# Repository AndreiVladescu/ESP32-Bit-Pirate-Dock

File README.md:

<div align="center">

# ESP32-Bit-Pirate-Hardware

</div>

**ESP32-Bit-Pirate-Dock** is an open-source carrier board for the Espressif ESP32-S3 DevKit, designed to complement the [ESP32-Bit-Pirate](https://github.com/geo-tp/ESP32-Bit-Pirate) firmware by [geo-tp](https://github.com/geo-tp).

It provides level and voltage translation between the 3.3V ESP32-S3 and external peripherals, with support for **1.8V**, **3.3V**, and **5V** operation. See the [Hardware status](#-hardware-status) section for the current revision, and grab the [fabrication files](#-manufacturing-and-assembly) to build your own.

<div align="center">

</div>

## 🙏 Thanks to PCBWay

A big thank you to [**PCBWay**](https://www.pcbway.com/) for sponsoring and manufacturing the PCBs for this project. Their high-quality fabrication and assembly made bringing this dock to life possible. You can buy the Dock [here](https://www.pcbway.com/project/shareproject/ESP32_Bit_Pirate_Dock_ca02ded7.html) and support the project.

<div align="center">

</div>

## ✨ Features

- **Level & voltage translation** between the 3.3V ESP32-S3 and external peripherals.
- **Selectable I/O voltage:** 1.8V, 3.3V, and 5V operation.
- **Carrier board** for the original ESP32-S3-DevKitC-1 as well as third-party clones.
- **Designed as a companion** to the [ESP32-Bit-Pirate](https://github.com/geo-tp/ESP32-Bit-Pirate) multi-protocol firmware.
- **Fully open-source hardware** — schematic, PCB layout, gerbers, and BOM included.
- **3D-printable enclosure** — two-piece FDM case provided.

## 📦 Supported Devices

| Device | Notes |
|--------|-------|
| **ESP32-S3-DevKitC-1** | Genuine Espressif devkit — the reference target for this design. |
| **ESP32-S3 DevKit clones** | Third-party boards work as long as the header pin layout and board dimensions match the official devkit. There is also support for clones which are 2.54mm wider, but you need to measure them to make sure everything will fit|

> [!NOTE]
> This project requires an **ESP32-S3 DevKit to be procured separately by the end user**.

## 🔧 Hardware status

Current hardware revision: **V3**

The markings on the PCB for the serial number `V0-YYWW-XXXXX` are as follows:

- version `0`
- year and week number when these PCBs were produced
- incrementing number of the current batch

An example PCB with these markings would be `V3-2613-00512`, where:

- version number is `3`
- the year is `2026`, and the week is `13`
- this is the `512th` PCB made in that respective week

<div align="center">

</div>

## 🚀 Getting Started

1. 🛒 **Source an ESP32-S3 DevKit**
   - Buy a genuine board from Espressif or a compatible clone.

2. 🏭 **Fabricate the dock**
   - Send the gerbers in `dock/gerbers/` to your PCB manufacturer of choice.
   - Use `dock/BOM.csv` to source the components for assembly.

3. 🖨️ **Print the enclosure** *(optional)*
   - Print the two-piece case from `dock/3d_models/` on an FDM printer with a 0.4 mm nozzle.

4. 🔌 **Assemble & seat the devkit**
   - Insert the ESP32-S3 DevKit into the headers and select your target I/O voltage (1.8V / 3.3V / 5V).

5. ⚡ **Flash the firmware**
   - Install [ESP32-Bit-Pirate](https://github.com/geo-tp/ESP32-Bit-Pirate) and start probing.

## 📂 Repository contents

- `dock/kicad/` — KiCad design files
- `dock/gerbers/` — PCB fabrication outputs
- `dock/schematic.pdf` — exported schematic reference
- `dock/BOM.csv` — bill of materials
- `dock/3d_models/` — 3D models for the dock and a WIP case
- `c5_adapter/` — KiCad design files for the companion C5 adapter board
- `images/` — presentation images

## 🌐 Open-source scope

This repository open-sources the dock hardware design, including:

- schematic and PCB layout source files
- fabrication outputs
- bill of materials
- project documentation and images included in this repository

## 🧩 Required external parts

This project requires an **ESP32-S3 DevKit to be procured separately by the end user**.

The ESP32-S3 DevKit is a third-party board/module and is **not included** as part of this hardware design repository unless explicitly stated. Vendor silicon, datasheets, trademarks, and separately licensed third-party materials remain the property of their respective owners.

These boards can be acquired through the official Espressif manufacturer and its stores, or through other third-party websites. If not buying a genuine one, make sure the dimensions fit one of the header pins on the board.

## 🛠️ PCB Design

### Top View

<div align="center">

</div>

## 🏭 Manufacturing and assembly

- To **fabricate the PCB**, use the files in `dock/gerbers/`.
- To **inspect or modify** the design, use the original KiCad source files in `dock/kicad/`.
- To **source components**, use `dock/BOM.csv`.

## 📐 Case Design

The current design uses two pieces, which can be printed using an FDM printer with a 0.4 mm nozzle.

<div align="center">

</div>

## 🤝 Related Project

This dock is built to complement [**ESP32-Bit-Pirate**](https://github.com/geo-tp/ESP32-Bit-Pirate) by [geo-tp](https://github.com/geo-tp) — an open-source firmware that turns your device into a multi-protocol hacker's tool, inspired by the [Bus Pirate](https://buspirate.com/) project.

## 📜 License

Hardware design files in this repository are licensed under the **CERN-OHL-W-2.0** license. See [LICENSE](LICENSE) for the full license text.

Documentation and images in this repository are licensed under **CC BY 4.0** unless otherwise noted.

Any third-party trademarks, datasheets, and separately licensed materials remain the property of their respective owners.

## ⚠️ Warning

> ⚠️ **Voltage Warning**: External peripherals should only be connected at the **selected translation voltage** (**1.8V**, **3.3V**, or **5V**).
>
> *   Do **not** connect peripherals using other voltage levels — doing so may **damage your ESP32 or the dock**.
> *   Always confirm the selected I/O voltage before powering up connected hardware.
>

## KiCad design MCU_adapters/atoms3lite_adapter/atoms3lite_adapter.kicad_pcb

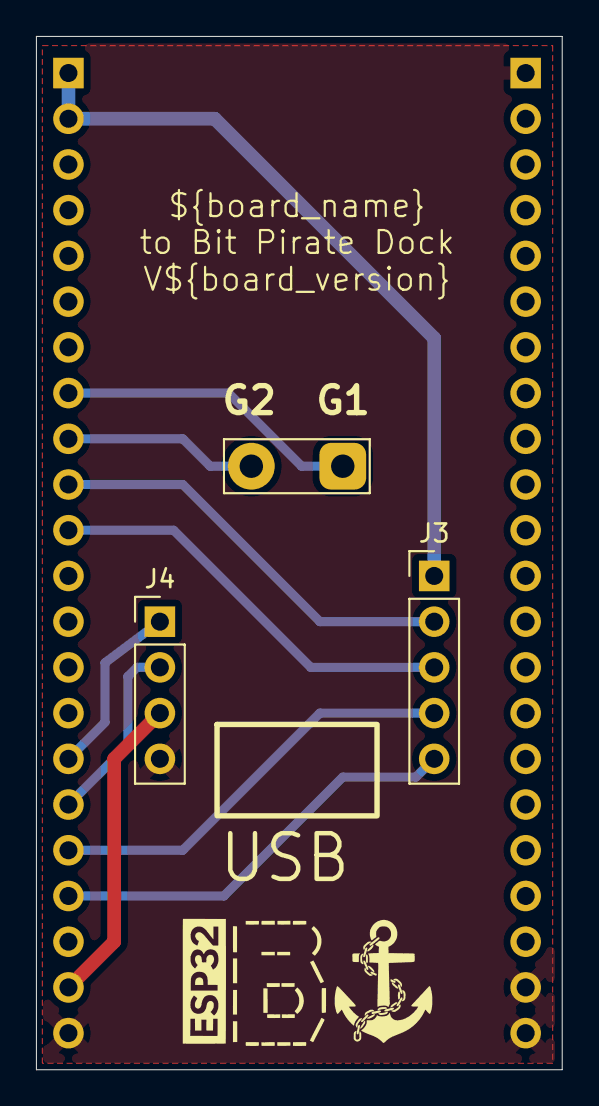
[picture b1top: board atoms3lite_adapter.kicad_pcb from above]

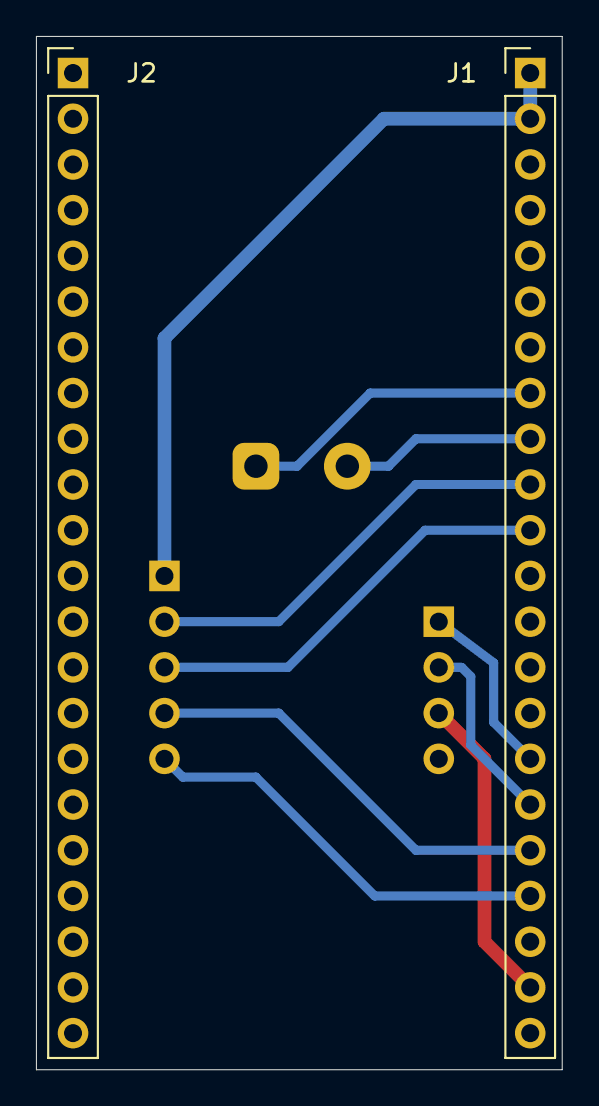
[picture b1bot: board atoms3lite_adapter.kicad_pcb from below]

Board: 2 copper layers, 29.2 x 57.4 mm, 7 parts (2 on the bottom side), 11 nets.

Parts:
G1: logoBP
G2: LOGO_USB
J1, J2: Conn_01x22; PinHeader_1x22_P2.54mm_Vertical
J3: Conn_01x05_Pin; PinHeader_1x05_P2.54mm_Vertical
J4: Conn_01x04_Pin; PinHeader_1x04_P2.54mm_Vertical
TP1: TestPoint_2Pole; TestPoint_2Pads_Pitch5.08mm_Drill1.3mm

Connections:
+3.3V: J1.1, J1.2, J3.1
+5V: J1.21, J4.3
/G1: J1.8, TP1.1
/G2: J1.9, TP1.2
/G5: J1.10, J3.2
/G6: J1.11, J3.3
/G7: J1.18, J3.4
/G8: J1.19, J3.5
/G38: J1.17, J4.2
/G39: J1.16, J4.1
GND: J1.22, J2.1, J2.21, J2.22, J4.4

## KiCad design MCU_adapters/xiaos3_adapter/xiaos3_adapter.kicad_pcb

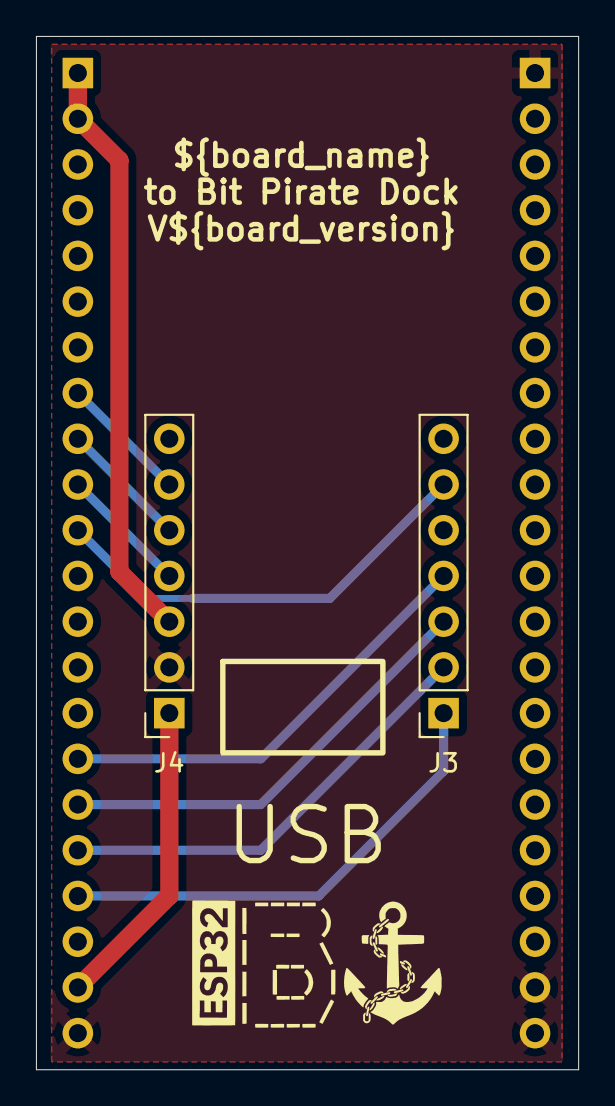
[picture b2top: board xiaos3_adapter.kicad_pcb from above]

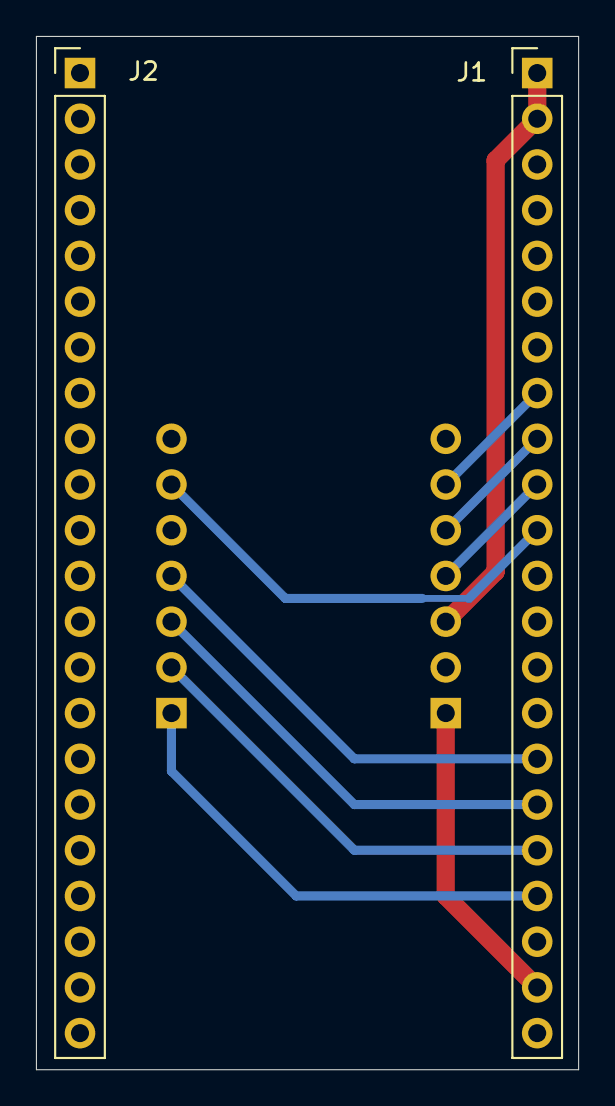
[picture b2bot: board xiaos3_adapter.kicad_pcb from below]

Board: 2 copper layers, 30.1 x 57.4 mm, 6 parts (2 on the bottom side), 11 nets.

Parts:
G1: logoBP
G2: LOGO_USB
J1, J2: Conn_01x22; PinHeader_1x22_P2.54mm_Vertical
J3, J4: Conn_01x07_Socket; PinSocket_1x07_P2.54mm_Vertical

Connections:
+3.3V: J1.1, J1.2, J4.3
+5V: J1.21, J4.1
/GPIO1: J1.19, J3.1
/GPIO2: J1.18, J3.2
/GPIO3: J1.17, J3.3
/GPIO4: J1.16, J3.4
/GPIO6: J1.11, J3.6
/GPIO7: J1.8, J4.6
/GPIO8: J1.9, J4.5
/GPIO9: J1.10, J4.4
GND: J1.22, J2.1, J2.21, J2.22, J4.2

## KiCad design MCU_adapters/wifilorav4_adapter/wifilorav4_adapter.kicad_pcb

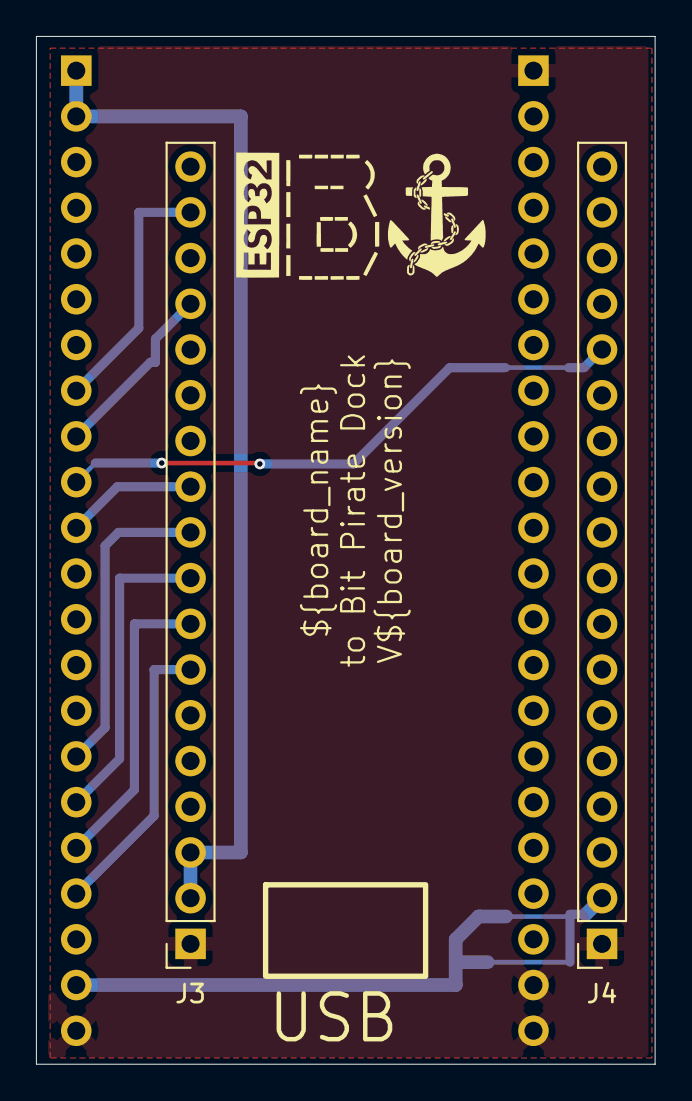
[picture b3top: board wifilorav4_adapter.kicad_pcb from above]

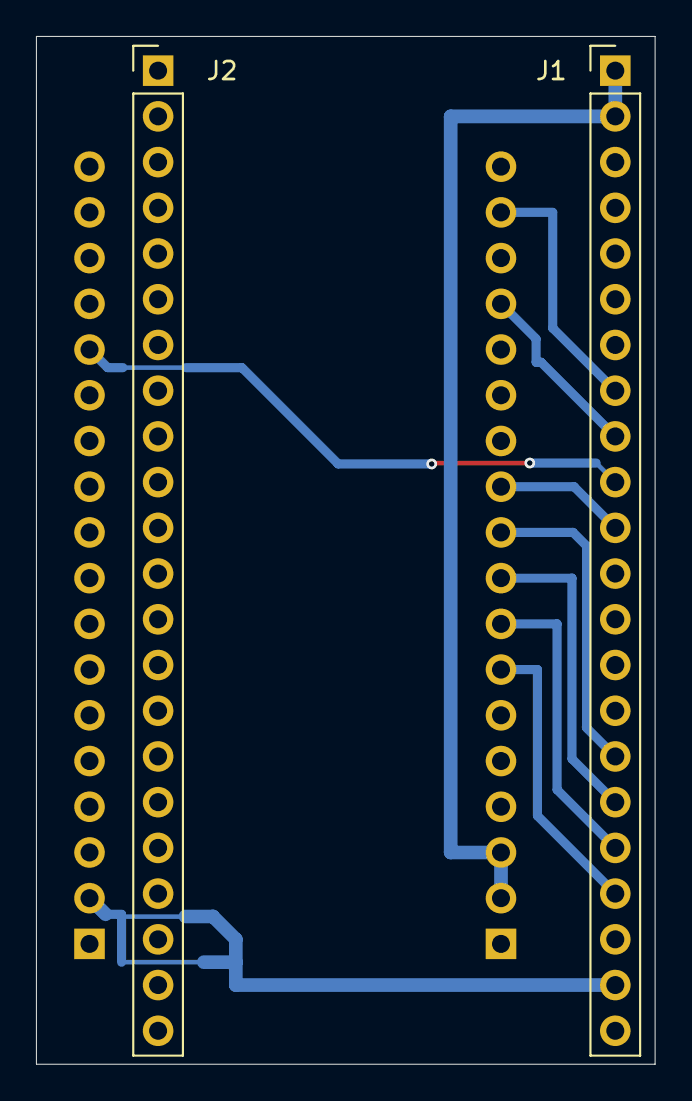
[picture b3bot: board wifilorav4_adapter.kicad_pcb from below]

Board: 2 copper layers, 34.4 x 57.1 mm, 6 parts (2 on the bottom side), 11 nets.

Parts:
G1: logoBP
G2: LOGO_USB
J1, J2: Conn_01x22; PinHeader_1x22_P2.54mm_Vertical
J3, J4: Conn_01x18_Socket; PinSocket_1x18_P2.54mm_Vertical

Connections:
+3.3V: J1.1, J1.2, J3.2, J3.3
+5V: J1.21, J4.2
/GPIO4: J1.9, J3.15
/GPIO6: J1.8, J3.17
/GPIO38: J1.11, J3.11
/GPIO39: J1.16, J3.10
/GPIO40: J1.17, J3.9
/GPIO41: J1.18, J3.8
/GPIO42: J1.19, J3.7
/GPIO48: J1.10, J4.14
GND: J1.22, J2.1, J2.21, J2.22, J3.1, J4.1

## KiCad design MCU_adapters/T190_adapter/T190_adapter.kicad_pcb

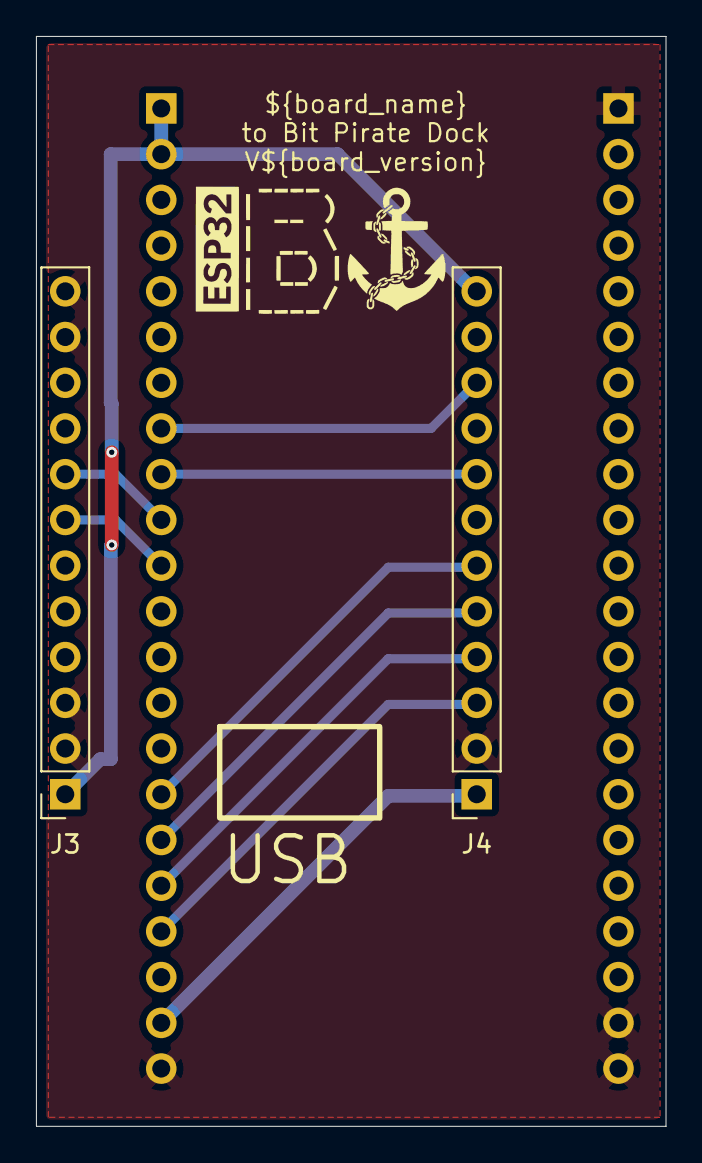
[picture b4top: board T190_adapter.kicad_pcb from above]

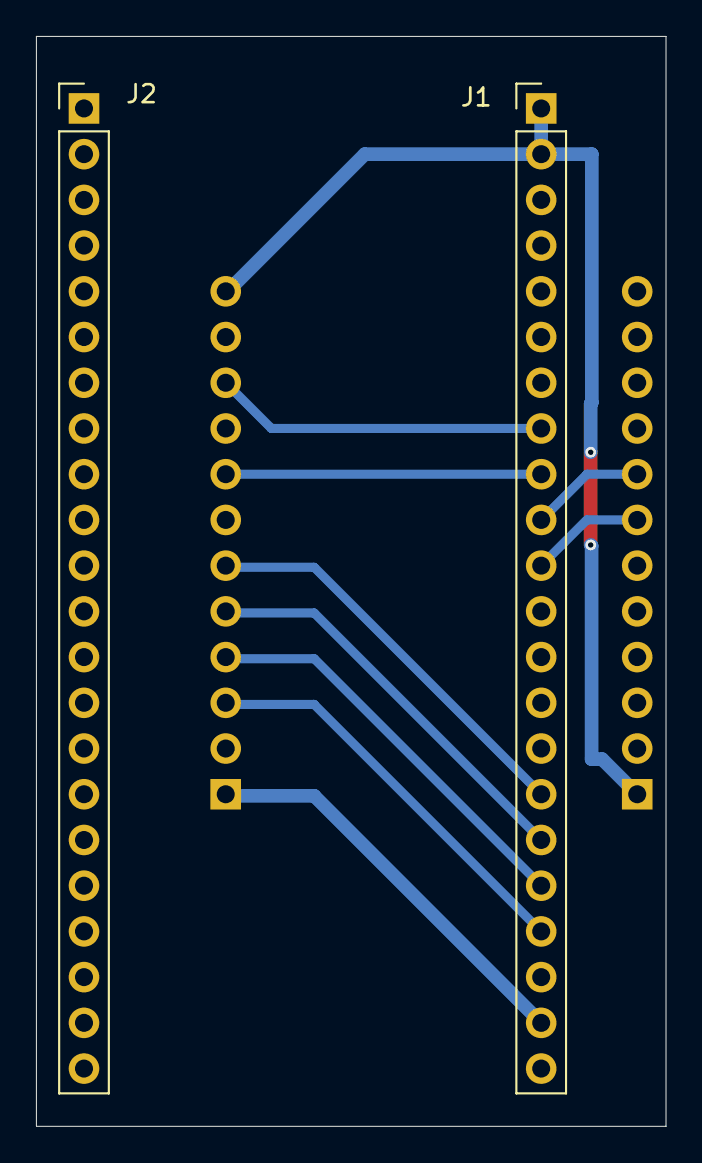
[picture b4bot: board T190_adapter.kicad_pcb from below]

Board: 2 copper layers, 35.0 x 60.6 mm, 6 parts (2 on the bottom side), 11 nets.

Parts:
G1: logoBP
G2: LOGO_USB
J1, J2: Conn_01x22; PinHeader_1x22_P2.54mm_Vertical
J3, J4: Conn_01x12_Socket; PinSocket_1x12_P2.54mm_Vertical

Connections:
+3.3V: J1.1, J1.2, J3.1, J4.12
+5V: J1.21, J4.1
/GPIO2: J1.8, J4.10
/GPIO4: J1.9, J4.8
/GPIO9: J1.16, J4.6
/GPIO10: J1.17, J4.5
/GPIO11: J1.18, J4.4
/GPIO12: J1.19, J4.3
/GPIO15: J1.11, J3.7
/GPIO16: J1.10, J3.8
GND: J1.22, J2.1, J2.21, J2.22, J3.2, J3.3, J3.11, J3.12, J4.2

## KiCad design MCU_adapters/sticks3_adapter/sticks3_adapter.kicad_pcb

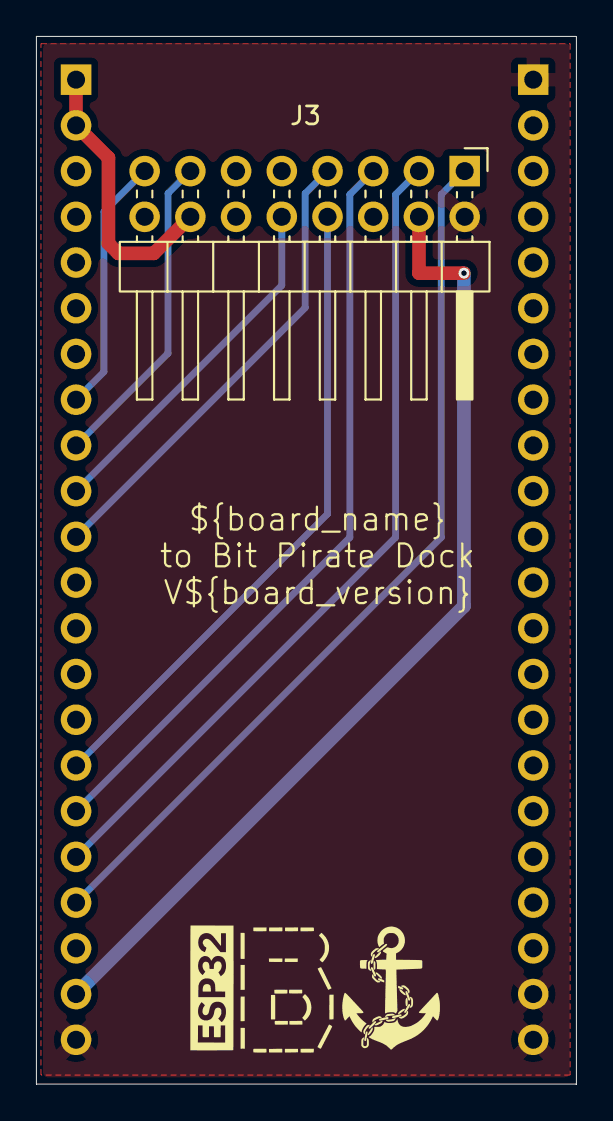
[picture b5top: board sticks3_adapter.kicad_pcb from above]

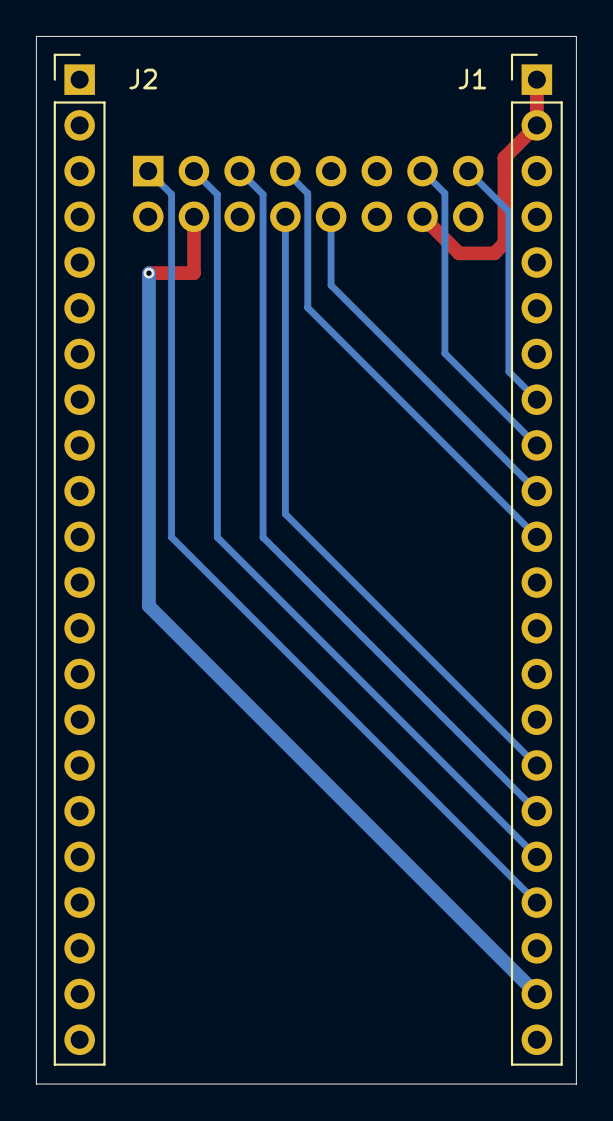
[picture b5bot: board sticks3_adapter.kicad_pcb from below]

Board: 2 copper layers, 30.0 x 58.2 mm, 4 parts (2 on the bottom side), 11 nets.

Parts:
G1: logoBP
J1, J2: Conn_01x22; PinHeader_1x22_P2.54mm_Vertical
J3: Conn_02x08_Odd_Even; PinHeader_2x08_P2.54mm_Horizontal

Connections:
+3.3V: J1.1, J1.2, J3.14
+5V: J1.21, J3.4
/G1: J1.16, J3.8
/G2: J1.9, J3.13
/G3: J1.8, J3.15
/G4: J1.18, J3.3
/G5: J1.19, J3.1
/G6: J1.17, J3.5
/G7: J1.11, J3.7
/G8: J1.10, J3.10
GND: J1.22, J2.1, J2.21, J2.22, J3.2

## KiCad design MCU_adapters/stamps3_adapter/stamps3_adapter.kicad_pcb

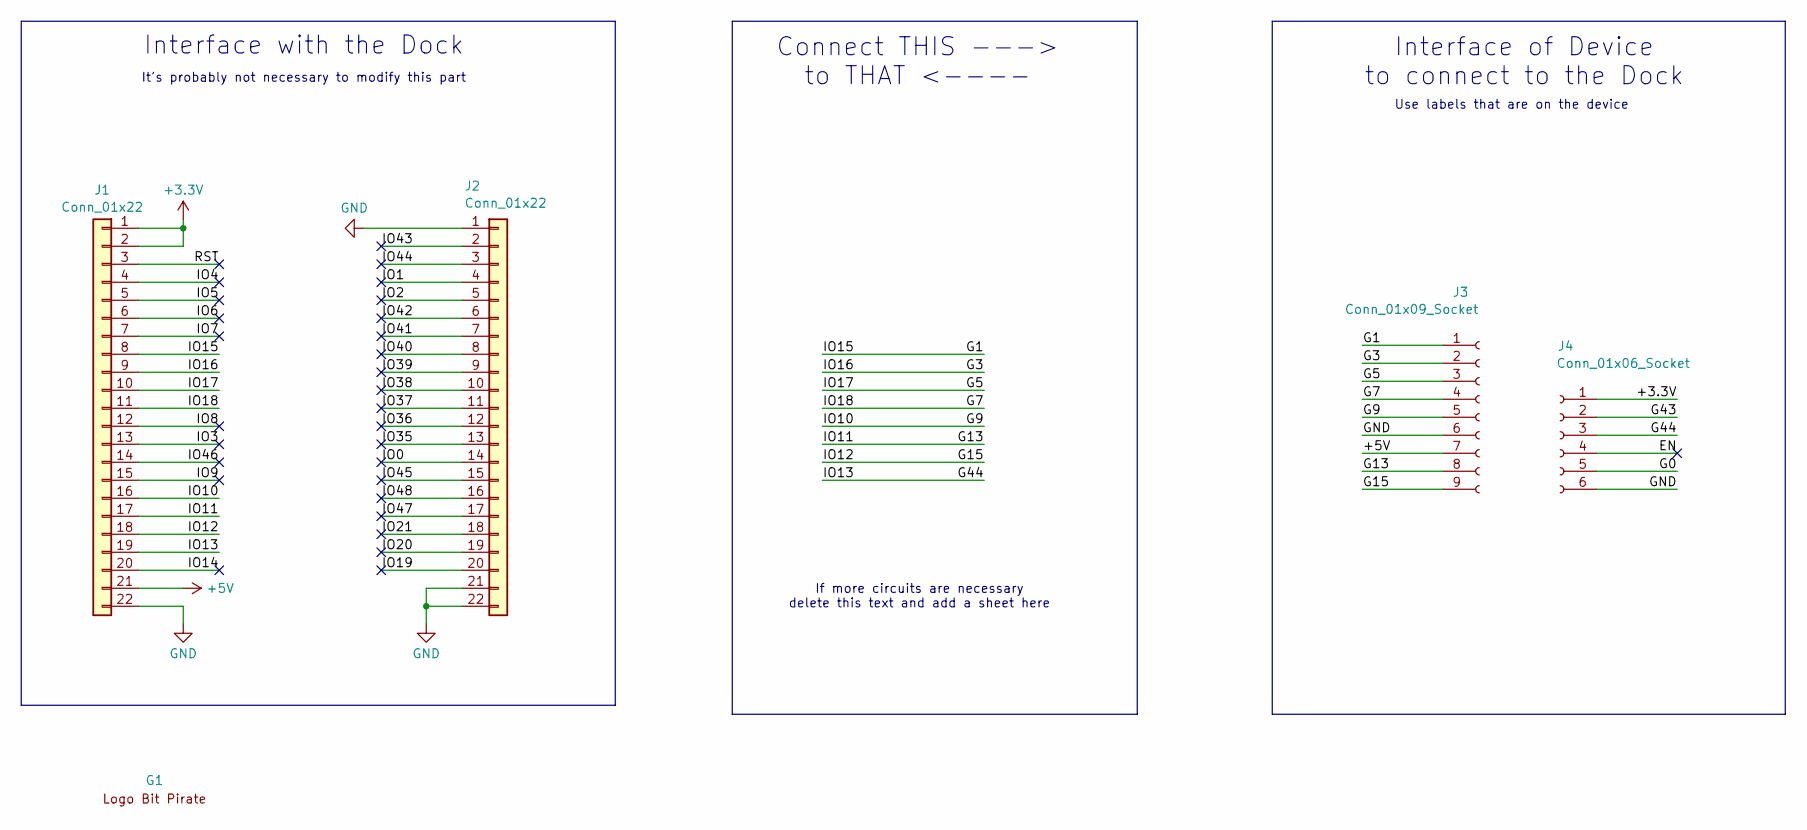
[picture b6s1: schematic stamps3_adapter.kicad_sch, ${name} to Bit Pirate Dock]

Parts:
G1: logoBP
J1, J2: Conn_01x22; PinHeader_1x22_P2.54mm_Vertical
J3: Conn_01x09_Socket; PinSocket_1x09_P2.54mm_Vertical
J4: Conn_01x06_Socket; PinSocket_1x06_P2.54mm_Vertical

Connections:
+3.3V: J1.1, J1.2, J4.1
+5V: J1.21, J3.7
/EN: J4.4
/G0: J4.5
/G1: J1.8, J3.1
/G3: J1.9, J3.2
/G5: J1.10, J3.3
/G7: J1.11, J3.4
/G9: J1.16, J3.5
/G13: J1.17, J3.8
/G15: J1.18, J3.9
/G43: J4.2
/G44: J1.19, J4.3
/IO0: J2.14
/IO1: J2.4
/IO2: J2.5
/IO3: J1.13
/IO4: J1.4
/IO5: J1.5
/IO6: J1.6
/IO7: J1.7
/IO8: J1.12
/IO9: J1.15
/IO14: J1.20
/IO19: J2.20
/IO20: J2.19
/IO21: J2.18
/IO35: J2.13
/IO36: J2.12
/IO37: J2.11
/IO38: J2.10
/IO39: J2.9
/IO40: J2.8
/IO41: J2.7
/IO42: J2.6
/IO43: J2.2
/IO44: J2.3
/IO45: J2.15
/IO46: J1.14
/IO47: J2.17
/IO48: J2.16
/RST: J1.3
GND: J1.22, J2.1, J2.21, J2.22, J3.6, J4.6

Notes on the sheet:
Use labels that are on the device
Connect THIS ---> to THAT <----
Interface of Device to connect to the Dock
It's probably not necessary to modify this part
Interface with the Dock
If more circuits are necessary delete this text and add a sheet here

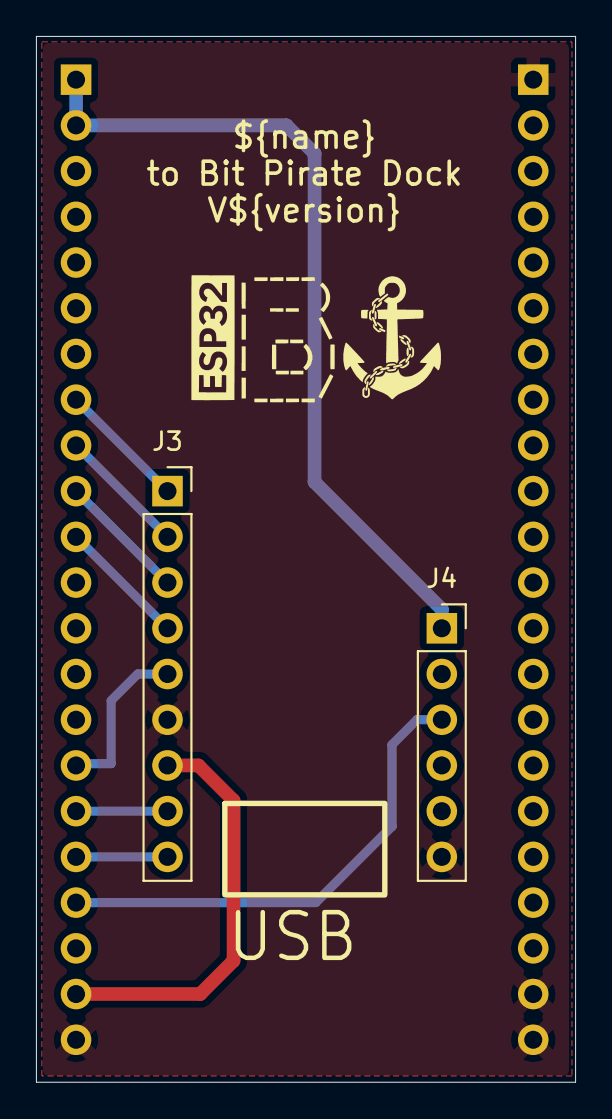
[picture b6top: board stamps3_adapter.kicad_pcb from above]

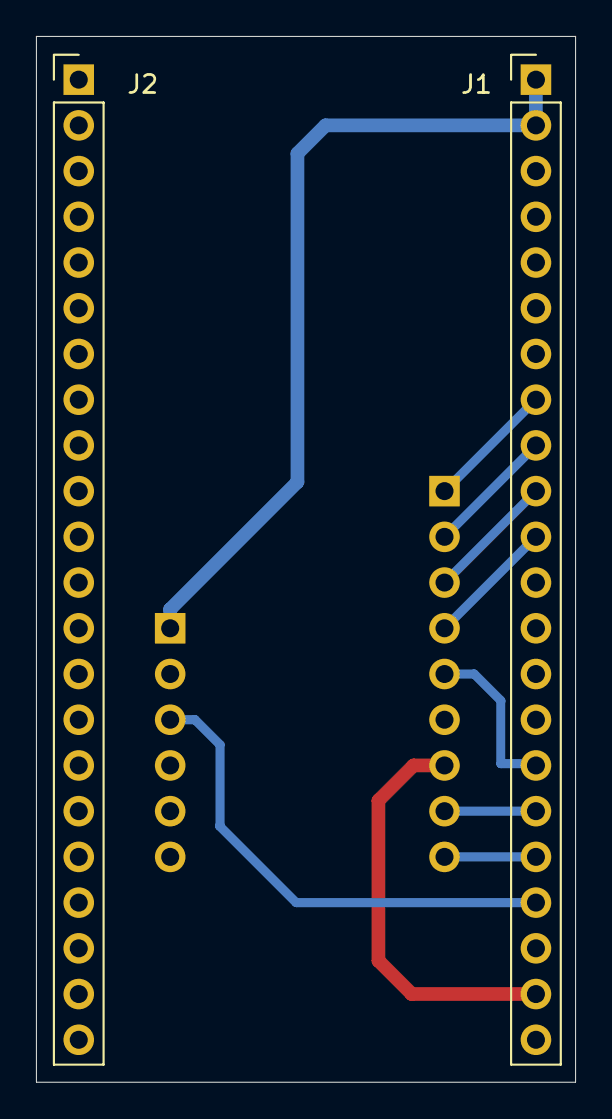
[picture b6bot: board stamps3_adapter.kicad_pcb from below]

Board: 2 copper layers, 30.0 x 58.1 mm, 6 parts (2 on the bottom side), 11 nets.

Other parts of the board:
G2: LOGO_USB

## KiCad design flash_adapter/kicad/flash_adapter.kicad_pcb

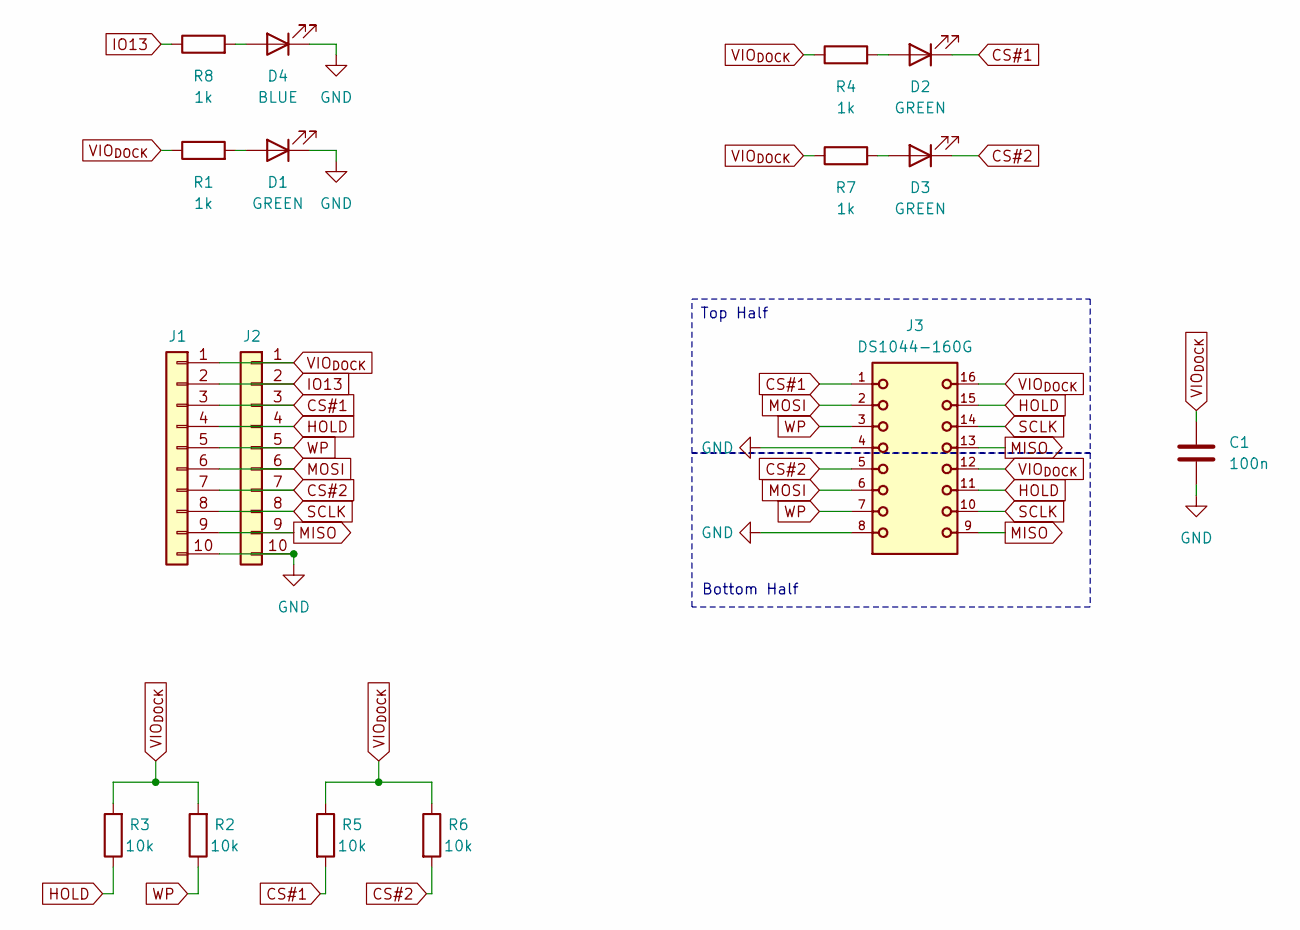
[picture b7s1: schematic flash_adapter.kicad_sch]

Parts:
C1: 100n; C_0805_2012Metric
D1, D2, D3: GREEN; LED_0805_2012Metric
D4: BLUE; LED_0805_2012Metric
J1: Conn_01x10; PinSocket_1x10_P2.54mm_Horizontal
J2: Conn_01x10; PinSocket_1x10_P2.54mm_Vertical
J3: DS1044-160G; CONNFLY_DS1044-160G
R1, R4, R7, R8: 1k; R_0805_2012Metric
R2, R3, R5, R6: 10k; R_0805_2012Metric

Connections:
CS#1: D2.1 (K), J1.3, J2.3, J3.1, R5.2
CS#2: D3.1 (K), J1.7, J2.7, J3.5, R6.2
GND: C1.2, D1.1 (K), D4.1 (K), J1.10, J2.10, J3.4, J3.8
HOLD: J1.4, J2.4, J3.11, J3.15, R3.1
IO13: J1.2, J2.2, R8.1
MISO: J1.9, J2.9, J3.9, J3.13
MOSI: J1.6, J2.6, J3.2, J3.6
unnamed: D1.2 (A), R1.2
unnamed: D2.2 (A), R4.2
unnamed: D3.2 (A), R7.2
unnamed: D4.2 (A), R8.2
SCLK: J1.8, J2.8, J3.10, J3.14
VIO_{DOCK}: C1.1, J1.1, J2.1, J3.12, J3.16, R1.1, R2.2, R3.2, R4.1, R5.1, R6.1, R7.1
WP: J1.5, J2.5, J3.3, J3.7, R2.1

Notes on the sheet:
Bottom Half
Top Half

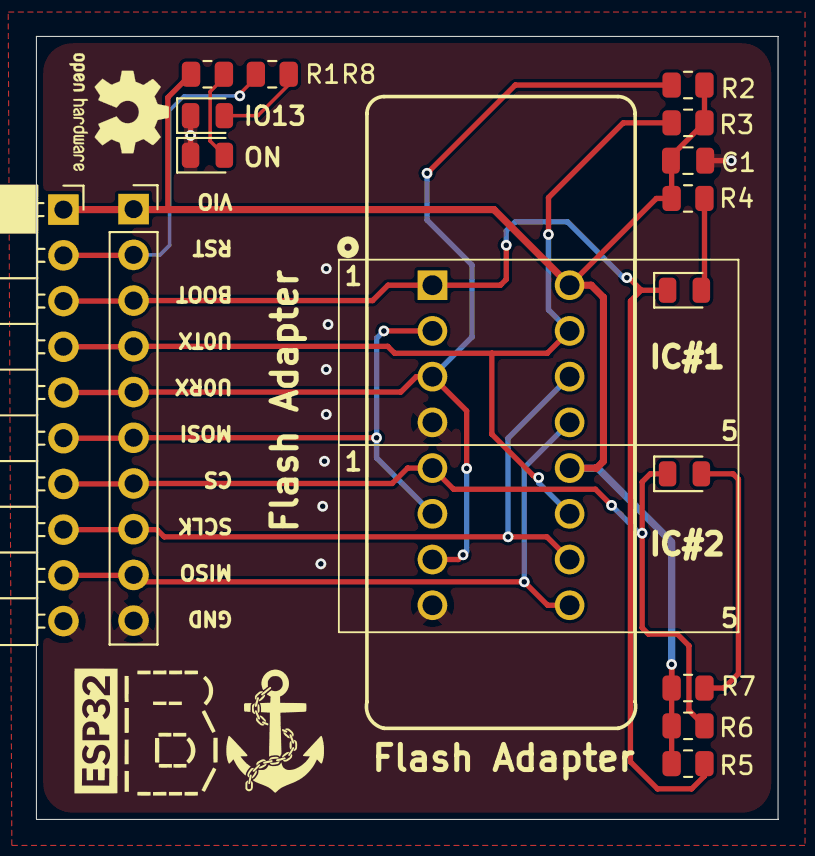
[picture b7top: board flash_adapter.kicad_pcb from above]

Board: 2 copper layers, 41.2 x 43.5 mm, 16 parts (0 on the bottom side), 14 nets.

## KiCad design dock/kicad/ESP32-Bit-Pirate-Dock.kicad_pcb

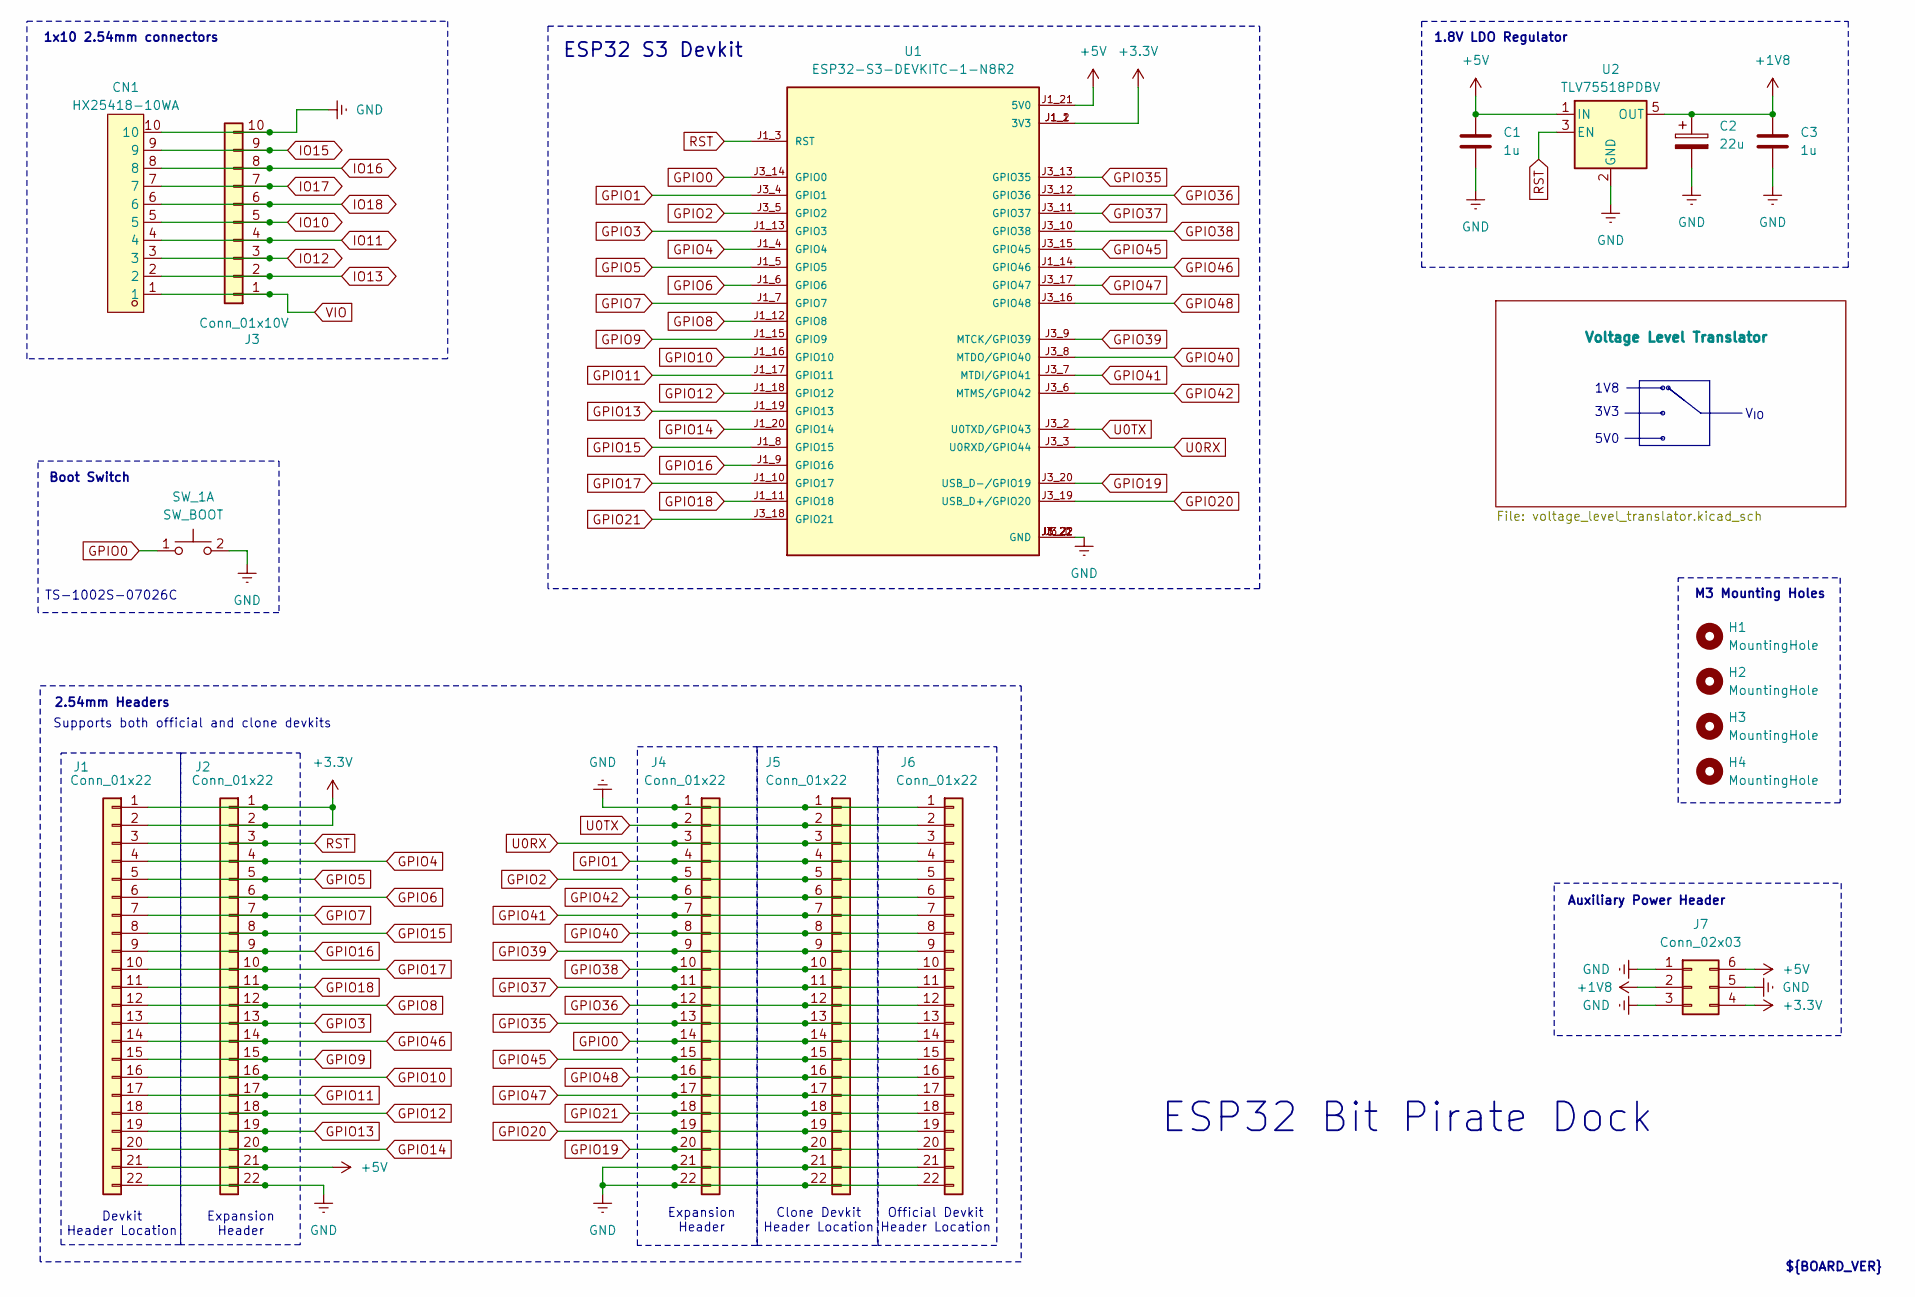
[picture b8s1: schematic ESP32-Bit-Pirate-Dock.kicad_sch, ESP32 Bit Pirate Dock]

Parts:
C1, C3: 1u; C_0805_2012Metric
C2: 22u; CP_Elec_5x4.5
CN1: HX25418-10WA; CONN-TH_HX25418-10WA; LCSC Part C704586
H1, H2, H3, H4: MountingHole; MountingHole_3.2mm_M3_DIN965_Pad_TopBottom
J1, J5, J6: Conn_01x22; PinSocket_1x22_P2.54mm_Vertical
J2, J4: Conn_01x22; PinHeader_1x22_P2.54mm_Vertical
J3: Conn_01x10V; PinSocket_1x10_P2.54mm_Vertical
J7: Conn_02x03; PinHeader_2x03_P2.54mm_Vertical
SW_1: SW_BOOT; SW_SPST_PTS645Sx43SMTR92
U1: ESP32-S3-DEVKITC-1-N8R2; XCVR_ESP32-S3-DEVKITC-1-N8R2; PARTREV V1
U2: TLV75518PDBV; SOT-23-5

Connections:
+1V8: C2.1, C3.1, J7.2, U2.5 (OUT); also elsewhere on the board
+3.3V: J1.1, J1.2, J2.1, J2.2, J7.4, U1.J1_1 (3V3), U1.J1_2 (3V3); also elsewhere on the board
+5V: C1.1, J1.21, J2.21, J7.6, U1.J1_21 (5V0), U2.1 (IN); also elsewhere on the board
GND: C1.2, C2.2, C3.2, CN1.10, J1.22, J2.22, J3.10, J4.1, J4.21, J4.22, J5.1, J5.21, J5.22, J6.1, J6.21, J6.22, J7.1, J7.3, J7.5, SW_1.2 (D), U1.J1_22 (GND), U1.J3_1 (GND), U1.J3_21 (GND), U1.J3_22 (GND), U2.2 (GND); also elsewhere on the board
GPIO0: J4.14, J5.14, J6.14, SW_1.1 (C), U1.J3_14 (GPIO0)
GPIO1: J4.4, J5.4, J6.4, U1.J3_4 (GPIO1)
GPIO2: J4.5, J5.5, J6.5, U1.J3_5 (GPIO2)
GPIO3: J1.13, J2.13, U1.J1_13 (GPIO3)
GPIO4: J1.4, J2.4, U1.J1_4 (GPIO4)
GPIO5: J1.5, J2.5, U1.J1_5 (GPIO5)
GPIO6: J1.6, J2.6, U1.J1_6 (GPIO6)
GPIO7: J1.7, J2.7, U1.J1_7 (GPIO7)
GPIO8: J1.12, J2.12, U1.J1_12 (GPIO8)
GPIO9: J1.15, J2.15, U1.J1_15 (GPIO9)
GPIO10: J1.16, J2.16, U1.J1_16 (GPIO10); also elsewhere on the board
GPIO11: J1.17, J2.17, U1.J1_17 (GPIO11); also elsewhere on the board
GPIO12: J1.18, J2.18, U1.J1_18 (GPIO12); also elsewhere on the board
GPIO13: J1.19, J2.19, U1.J1_19 (GPIO13); also elsewhere on the board
GPIO14: J1.20, J2.20, U1.J1_20 (GPIO14)
GPIO15: J1.8, J2.8, U1.J1_8 (GPIO15); also elsewhere on the board
GPIO16: J1.9, J2.9, U1.J1_9 (GPIO16); also elsewhere on the board
GPIO17: J1.10, J2.10, U1.J1_10 (GPIO17); also elsewhere on the board
GPIO18: J1.11, J2.11, U1.J1_11 (GPIO18); also elsewhere on the board
GPIO19: J4.20, J5.20, J6.20, U1.J3_20 (USB_D-/GPIO19)
GPIO20: J4.19, J5.19, J6.19, U1.J3_19 (USB_D+/GPIO20)
GPIO21: J4.18, J5.18, J6.18, U1.J3_18 (GPIO21)
GPIO35: J4.13, J5.13, J6.13, U1.J3_13 (GPIO35)
GPIO36: J4.12, J5.12, J6.12, U1.J3_12 (GPIO36)
GPIO37: J4.11, J5.11, J6.11, U1.J3_11 (GPIO37)
GPIO38: J4.10, J5.10, J6.10, U1.J3_10 (GPIO38)
GPIO39: J4.9, J5.9, J6.9, U1.J3_9 (MTCK/GPIO39)
GPIO40: J4.8, J5.8, J6.8, U1.J3_8 (MTDO/GPIO40)
GPIO41: J4.7, J5.7, J6.7, U1.J3_7 (MTDI/GPIO41)
GPIO42: J4.6, J5.6, J6.6, U1.J3_6 (MTMS/GPIO42)
GPIO45: J4.15, J5.15, J6.15, U1.J3_15 (GPIO45)
GPIO46: J1.14, J2.14, U1.J1_14 (GPIO46)
GPIO47: J4.17, J5.17, J6.17, U1.J3_17 (GPIO47)
GPIO48: J4.16, J5.16, J6.16, U1.J3_16 (GPIO48)
IO10: CN1.5, J3.5; also elsewhere on the board
IO11: CN1.4, J3.4; also elsewhere on the board
IO12: CN1.3, J3.3; also elsewhere on the board
IO13: CN1.2, J3.2; also elsewhere on the board
IO15: CN1.9, J3.9; also elsewhere on the board
IO16: CN1.8, J3.8; also elsewhere on the board
IO17: CN1.7, J3.7; also elsewhere on the board
IO18: CN1.6, J3.6; also elsewhere on the board
RST: J1.3, J2.3, U1.J1_3 (RST), U2.3 (EN)
U0RX: J4.3, J5.3, J6.3, U1.J3_3 (U0RXD/GPIO44)
U0TX: J4.2, J5.2, J6.2, U1.J3_2 (U0TXD/GPIO43)
VIO: CN1.1, J3.1; also elsewhere on the board

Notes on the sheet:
Boot Switch
M3 Mounting Holes
${BOARD_VER}
1.8V LDO Regulator
TS-1002S-07026C
1x10 2.54mm connectors
Auxiliary Power Header
Clone Devkit Header Location
Expansion Header
Official Devkit Header Location
2.54mm Headers
Devkit Header Location
5V0
3V3
ESP32 S3 Devkit
1V8
V_{IO}
Supports both official and clone devkits
ESP32 Bit Pirate Dock
